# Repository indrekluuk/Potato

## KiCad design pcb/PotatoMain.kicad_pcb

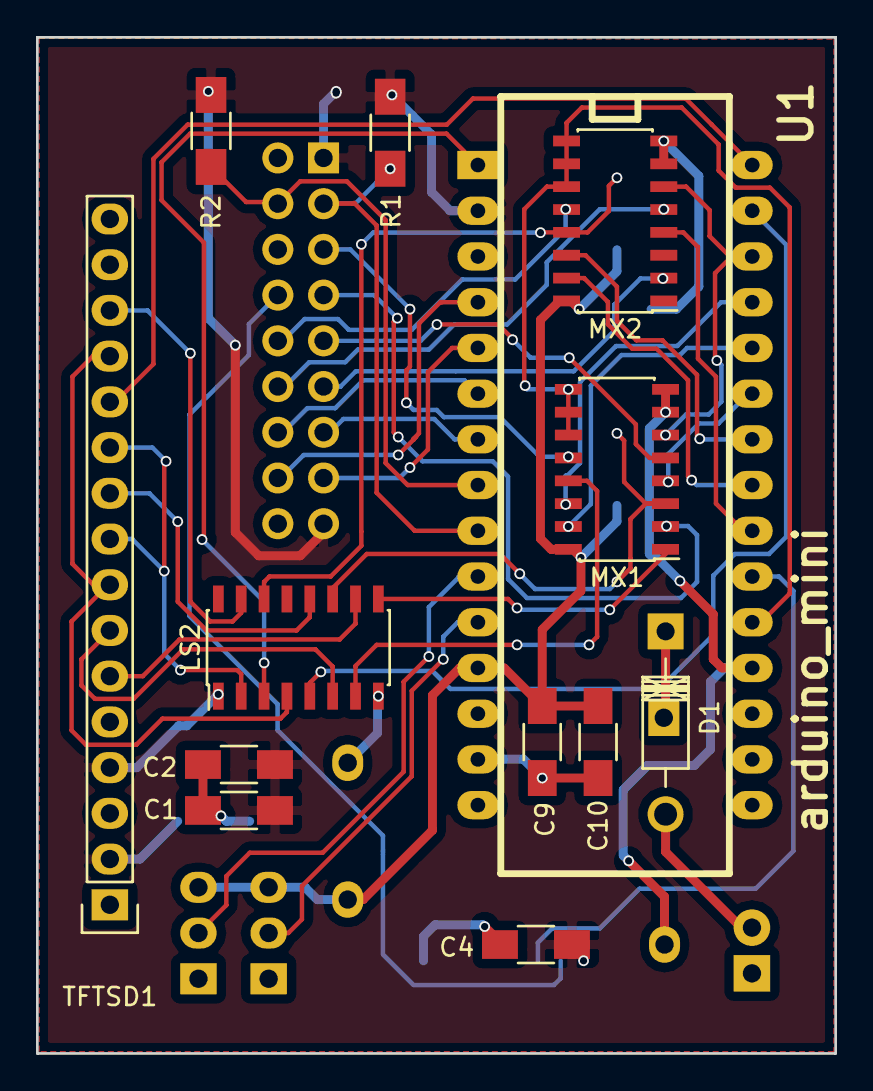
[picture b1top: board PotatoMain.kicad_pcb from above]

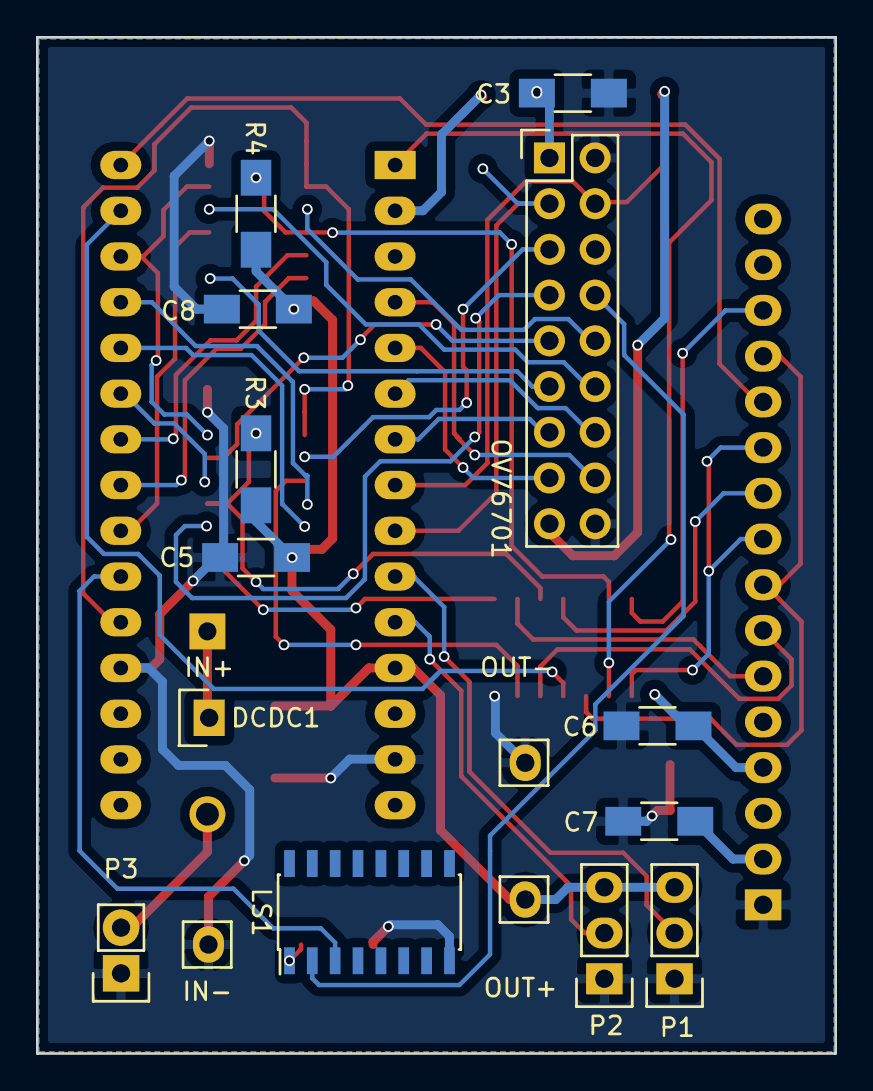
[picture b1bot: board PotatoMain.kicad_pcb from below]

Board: 2 copper layers, 44.4 x 56.5 mm, 26 parts (13 on the bottom side), 42 nets.

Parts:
C1, C2, C9, C10: 10-100u; C_1206_HandSoldering
C3: 1u; C_1206_HandSoldering
C4, C5, C6, C8: 0.1u; C_1206_HandSoldering
C7: 10u; C_1206_HandSoldering
D1: D; Diode_DO-41_SOD81_Horizontal_RM10
DCDC1: DcDcConverter; DcDc5VUp
LS1, LS2: LevelShifter_74HC4050D; SOIC-16_3.9x9.9mm_Pitch1.27mm
MX1, MX2: MuxDemux_74HC4053; SOIC-16_3.9x9.9mm_Pitch1.27mm
OV76701: Camera_OV7670; Pin_Header_Straight_2x09
P1, P2: CONN_01X03; Pin_Header_Straight_1x03
P3: CONN_01X02; Pin_Header_Straight_1x02
R1, R2, R3, R4: 10k; R_1206_HandSoldering
TFTSD1: TFT_1.8inch_and_SDCard; Pin_Header_Straight_1x16
U1: arduino_mini

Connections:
+3V3: C1.1, C2.1, C3.1, C4.2, C6.1, C7.1, LS1.1, LS2.1, OV76701.1, OV76701.17, R1.1, R2.1, TFTSD1.2, TFTSD1.4, U1.2
+5V: C5.2, C8.2, C9.1, C10.1, DCDC1.3, MX1.16, MX2.16, P1.3, P2.3, R3.1, R4.1, U1.12
/Pixel_0: OV76701.16, U1.4
/Pixel_1: OV76701.15, U1.5
/Pixel_2: OV76701.14, U1.6
/Pixel_3: OV76701.13, U1.7
/Pixel_4: MX2.5, OV76701.12
/Pixel_5: MX2.2, OV76701.11
/Pixel_6: MX2.12, OV76701.10
/Pixel_7: MX1.5, OV76701.9
GND: C1.2, C2.2, C3.2, C4.1, C5.1, C6.2, C7.2, C8.1, C9.2, C10.2, DCDC1.2, DCDC1.4, LS1.8, LS2.8, MX1.7, MX1.8, MX2.7, MX2.8, OV76701.2, OV76701.18, P1.1, P2.1, P3.1, TFTSD1.1, U1.14, U1.19
unnamed: D1.1, DCDC1.1
unnamed: D1.2, P3.2
unnamed: LS1.2, OV76701.8
unnamed: LS1.3, U1.21
unnamed: LS2.2, TFTSD1.9, TFTSD1.11
unnamed: LS2.3, U1.1
unnamed: LS2.4, TFTSD1.8, TFTSD1.13
unnamed: LS2.5, U1.29
unnamed: LS2.6, TFTSD1.7
unnamed: LS2.7, MX1.13
unnamed: LS2.9, MX1.1
unnamed: LS2.10, TFTSD1.6
unnamed: LS2.11, MX1.3, R3.2
unnamed: LS2.12, TFTSD1.10
unnamed: LS2.14, MX2.13, R4.2
unnamed: LS2.15, TFTSD1.14
unnamed: MX1.2, OV76701.7
unnamed: MX1.4, U1.25
unnamed: MX1.6, MX2.6, U1.28
unnamed: MX1.9, MX1.10, MX1.11, MX2.9, MX2.10, MX2.11, U1.20
unnamed: MX1.12, OV76701.5
unnamed: MX1.14, U1.27
unnamed: MX1.15, U1.26
unnamed: MX2.4, U1.22
unnamed: MX2.14, U1.24
unnamed: MX2.15, U1.23
unnamed: OV76701.3, R1.2, U1.9
unnamed: OV76701.4, R2.2, U1.8
unnamed: P1.2, U1.10
unnamed: P2.2, U1.11
unnamed: TFTSD1.12, U1.30

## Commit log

2017-02-25 renamed project name
2017-03-04 PCB routed
2017-03-04 made PCB smaller
